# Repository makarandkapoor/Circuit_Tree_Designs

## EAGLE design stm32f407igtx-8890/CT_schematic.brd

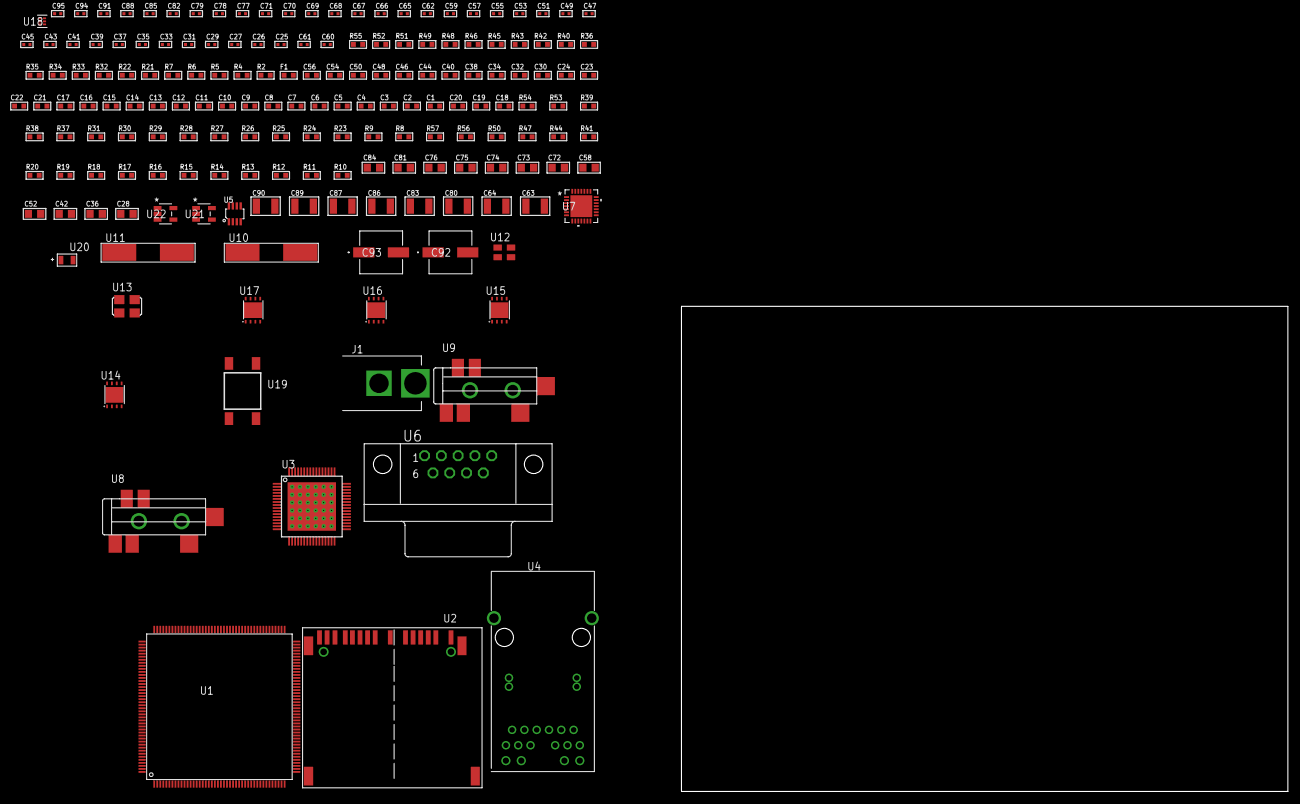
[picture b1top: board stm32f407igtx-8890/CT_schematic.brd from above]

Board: 2 copper layers, 100.0 x 80.0 mm, 174 parts (0 on the bottom side), 99 nets, no tracks yet.

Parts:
C1, C24, C30, C32, C34, C38, C40, C44, C46, C48, C50, C54, C56: 1e-06; C0603
C2, C3, C4, C5, C6, C7, C8, C9, C10, C11, C12, C13, C14, C15, C16, C17, C21, C22: 1e-07; C0603
C18: 4.7e-06; C0603
C19, C20: 2.2e-06; C0603
C23: 1e-08; C0603
C25, C26: 1e-11; C0402
C27, C29, C31, C33, C35, C39, C41, C45, C47, C49, C51, C55, C57, C62, C67, C68, C69, C70, C71, C91: 1e-07; C0402
C28, C36, C42, C52, C58, C72, C73, C74, C75, C76, C81, C84: 1e-05; C0805
C37, C43, C53, C59, C77, C78, C79, C82, C85, C88, C94, C95: 1e-08; C0402
C60, C61: 2.7e-11; C0402
C63, C64: 2.2e-05; C1210
C65, C66: 1e-09; C0402
C80, C83, C86, C87, C89, C90: 1e-05; C1210
C92, C93: 0.0001; EXV-9H
F1: 240.0; L0603
J1: PJ-037B; PJ-037B_PACKAGE
R2, R43, R46, R49, R52: 1000.0; R0603
R4, R5: 4700.0; R0603
R6, R7: 2200.0; R0603
R8, R9, R23, R25, R26, R27, R28, R29, R30, R31, R53, R54: 10000.0; R0603
R10, R11, R12, R13, R14, R15, R16, R17, R18, R19, R20, R41, R44, R47, R50: 100000.0; R0603
R21, R22: 200.0; R0603
R24: 11000.0; R0603
R32, R34: 5760.0; R0603
R33, R35: 2490.0; R0603
R36: 120.0; R0603
R37, R38, R39: 47000.0; R0603
R40: 680.0; R0603
R42: 100.0; R0603
R45: 806.0; R0603
R48: 1500.0; R0603
R51: 2231.0; R0603
R55: 9100.0; R0603
R56: 680000.0; R0603
R57: 120000.0; R0603
U1: STM32F407IGT6; LQFP176
U2: 10100565
U3: DP83867IRPAPT; HTQFP-64-EXP
U4: 7499511611A
U5: MAX3051EKA+T; SOT-23-8
U6: 182-009-113R531; 182-009-MALE
U7: WM8731CLSEFL; QFN-28
U8, U9: SJ-43515TS-SMT-TR
U10, U11: ABLS-25.000MHZ-B2F-T
U12: ASEK-32.768KHz-ECST; ASEK
U13: ASFL1-12.288MHZ-EC-T; ASFL1
U14, U15, U16, U17: LP3878SDX-ADJ/NOPB; WSON-8
U18: TPS3895ADRYR; SON-6
U19: 4-1437565-2; SW_4-1437565-2
U20: Q65110A2395; LGM67K-G1J2-24-Z
U21, U22: nc7sz125m5x; NC7SZ125M5X

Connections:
CLK_CRYSTAL_U1_29: C25.1, U1.29, U10.1
CLK_CRYSTAL_U1_30: C26.1, U1.30, U10.2
CLK_CRYSTAL_U3_18: C60.1, U3.18, U11.2
CLK_CRYSTAL_U3_19: C61.1, U3.19, U11.1
CLK_U1_9: U1.9, U12.3
CLK_U7_1: U7.1, U13.3
GND: C1.2, C2.2, C3.2, C4.2, C5.2, C6.2, C7.2, C8.2, C9.2, C10.2, C11.2, C12.2, C13.2, C14.2, C15.2, C16.2, C17.2, C18.2, C19.2, C20.2, C21.2, C22.2, C23.2, C24.2, C25.2, C26.2, C27.2, C28.2, C29.2, C30.2, C31.2, C32.2, C33.2, C34.2, C35.2, C36.2, C37.2, C38.2, C39.2, C40.2, C41.2, C42.2, C43.2, C44.2, C45.2, C46.2, C47.2, C48.2, C49.2, C50.2, C51.2, C52.2, C53.2, C54.2, C55.2, C56.2, C57.2, C58.2, C59.2, C60.2, C61.2, C62.2, C66.2, C67.2, C68.2, C69.2, C70.2, C71.2, C72.2, C73.2, C74.2, C75.2, C76.2, C77.2, C78.2, C79.2, C80.2, C81.2, C82.2, C83.2, C84.2, C85.2, C86.2, C87.2, C88.2, C89.2, C90.2, C91.2, C92.2, C93.2, C94.2, C95.2, J1.2, R2.2, R8.2, R24.2, R25.2, R26.2, R27.2, R28.2, R29.2, R30.2, R31.2, R33.2, R35.2, R37.2, R38.2, R39.2, R43.2, R46.2, R49.2, R52.2, R55.2, R57.2, U1.14, U1.22, U1.37, U1.48, U1.61, U1.71, U1.90, U1.102, U1.113, U1.126, U1.135, U1.148, U1.158, U2.6, U2.10, U2.12, U2.16, U2.17, U2.20, U2.21, U3.EXP, U4.17, U4.20, U4.Z1, U4.Z2, U5.2, U5.8, U6.5, U7.4, U7.15, U7.19, U7.25, U7.26, U7.29, U8.1, U9.1, U12.2, U13.2, U14.3, U14.PAD, U15.3, U15.PAD, U16.3, U16.PAD, U17.3, U17.PAD, U18.2, U20.C, U21.1, U21.3, U22.1, U22.3
NET_U1_31: R5.1, U1.31, U22.4
NET_U1_33: R6.1, U1.33, U3.20
NET_U1_39: C21.1, C22.1, C23.1, C24.1, F1.1, U1.38, U1.39
NET_U1_42: R7.1, U1.42, U3.21
NET_U1_81: C19.1, U1.81
NET_U1_125: C20.1, U1.125
NET_U1_166: R8.1, U1.166
NET_U1_171: R9.1, U1.171
NET_U1_176: U19.3, U19.4
NET_U2_1: R12.1, U2.1
NET_U2_2: R11.1, U2.2
NET_U2_18: U2.18, U2.19
NET_U3_15: R24.1, U3.15
NET_U3_24: R30.1, U3.24
NET_U3_25: R31.1, U3.25
NET_U3_31: R26.1, U3.31
NET_U3_32: R27.1, U3.32
NET_U3_33: R28.1, U3.33
NET_U3_34: R29.1, U3.34
NET_U3_40: R25.1, U3.40
NET_U3_48: R34.1, R35.1, U3.48
NET_U3_59: R4.1, U3.59, U21.4
NET_U3_60: R23.1, U3.60
NET_U4_2: U3.11, U4.2
NET_U4_3: U3.10, U4.3
NET_U4_4: U3.5, U4.4
NET_U4_5: U3.6, U4.5
NET_U4_6: C29.1, U4.1, U4.6, U4.7, U4.12
NET_U4_8: U3.13, U4.8
NET_U4_9: U3.14, U4.9
NET_U4_10: U3.3, U4.10
NET_U4_11: U3.2, U4.11
NET_U4_18: R21.1, U4.18
NET_U4_19: R22.1, U4.19
NET_U5_6: R36.2, U5.6
NET_U6_2: R36.2, U5.6, U6.2
NET_U6_3: R36.1, U5.7, U6.3
NET_U7_20: C71.1, C76.1, U7.20
NET_U8_2: C64.1, R38.1, U8.2
NET_U8_5: C63.1, R37.1, U8.5
NET_U9_5: C65.1, C66.1, R39.1, R40.1, U9.5
NET_U14_1: C79.1, U14.1
NET_U14_6: R42.2, R43.1, U14.6
NET_U14_8: R41.1, U14.8
NET_U15_1: C82.1, U15.1
NET_U15_6: R45.2, R46.1, U15.6
NET_U15_8: R44.1, U15.8
NET_U16_1: C85.1, U16.1
NET_U16_6: R48.2, R49.1, U16.6
NET_U16_8: R47.1, U16.8
NET_U17_1: C88.1, U17.1
NET_U17_6: R51.2, R52.1, U17.6
NET_U17_8: R50.1, U17.8
NET_U18_1: R54.1, R55.1, U18.1
NET_U18_3: R56.2, R57.1, U18.3
NET_U18_4: R53.1, U18.4, U21.2, U22.2
NET_U19_1: R2.1, U19.1, U19.2
PROC_CAN1_RX: U1.11, U5.4
PROC_CAN1_TX: U1.123, U5.1
PROC_ETH_COL: U1.44, U3.55
PROC_ETH_CRS: U1.40, U3.56
PROC_ETH_RXD0: R32.1, R33.1, U1.54, U3.44
PROC_ETH_RXD1: U1.55, U3.45
PROC_ETH_RXD2: U1.56, U3.46
PROC_ETH_RXD3: U1.57, U3.47
PROC_ETH_RX_CLK: U1.41, U3.43
PROC_ETH_RX_DV: U1.53, U3.53
PROC_ETH_RX_ER: U1.12, U3.54
PROC_ETH_TXD0: U1.92, U3.38
PROC_ETH_TXD1: U1.93, U3.37
PROC_ETH_TXD2: U1.34, U3.36
PROC_ETH_TXD3: U1.1, U3.35
PROC_ETH_TX_CLK: U1.35, U3.30
PROC_ETH_TX_EN: U1.80, U3.52
PROC_I2S2_CK: U1.79, U7.7
PROC_I2S2_EXT_SD: U1.94, U7.10
PROC_I2S2_SD: U1.95, U7.8
PROC_I2S2_WS: U1.131, U7.9, U7.11
PROC_SDIO_CK: R10.1, U1.141, U2.8
PROC_SDIO_D0: R13.1, U1.117, U2.4
PROC_SDIO_D1: R14.1, U1.118, U2.3
PROC_SDIO_D2: R15.1, U1.139, U2.15
PROC_SDIO_D3: R16.1, U1.140, U2.14
PROC_SDIO_D4: R17.1, U1.167, U2.13
PROC_SDIO_D5: R18.1, U1.168, U2.11
PROC_SDIO_D6: R19.1, U1.115, U2.7
PROC_SDIO_D7: R20.1, U1.116, U2.5
VCC_S1_12V3: C80.1, C83.1, C86.1, C89.1, C92.1, C93.1, J1.1, R41.2, R44.2, R47.2, R50.2, U14.4, U15.4, U16.4, U17.4
VCC_TIER1_1V1: C44.1, C45.1, C46.1, C47.1, C48.1, C49.1, C50.1, C51.1, C52.1, C53.1, C81.1, R42.1, U3.8, U3.29, U3.42, U3.58, U14.5
VCC_TIER1_1V8: C27.1, C28.1, C54.1, C55.1, C56.1, C57.1, C58.1, C59.1, C67.1, C69.1, C70.1, C72.1, C74.1, C75.1, C84.1, C94.1, C95.1, R10.2, R11.2, R12.2, R13.2, R14.2, R15.2, R16.2, R17.2, R18.2, R19.2, R20.2, R45.1, U2.9, U3.17, U3.64, U7.5, U7.12, U7.18, U15.5, U21.5, U22.5
VCC_TIER1_2V5: C38.1, C39.1, C40.1, C41.1, C42.1, C43.1, C87.1, R48.1, U3.4, U3.12, U16.5
VCC_TIER1_3V3: C1.1, C2.1, C3.1, C4.1, C5.1, C6.1, C7.1, C8.1, C9.1, C10.1, C11.1, C12.1, C13.1, C14.1, C15.1, C16.1, C17.1, C18.1, C30.1, C31.1, C32.1, C33.1, C34.1, C35.1, C36.1, C37.1, C62.1, C68.1, C73.1, C77.1, C78.1, C90.1, C91.1, F1.2, R4.2, R5.2, R6.2, R7.2, R9.2, R23.2, R32.2, R34.2, R51.1, R53.2, R54.2, R56.1, U1.6, U1.15, U1.23, U1.36, U1.49, U1.62, U1.72, U1.82, U1.91, U1.103, U1.114, U1.127, U1.136, U1.149, U1.159, U1.172, U3.23, U3.41, U3.57, U5.3, U7.3, U12.4, U13.4, U17.5, U18.6

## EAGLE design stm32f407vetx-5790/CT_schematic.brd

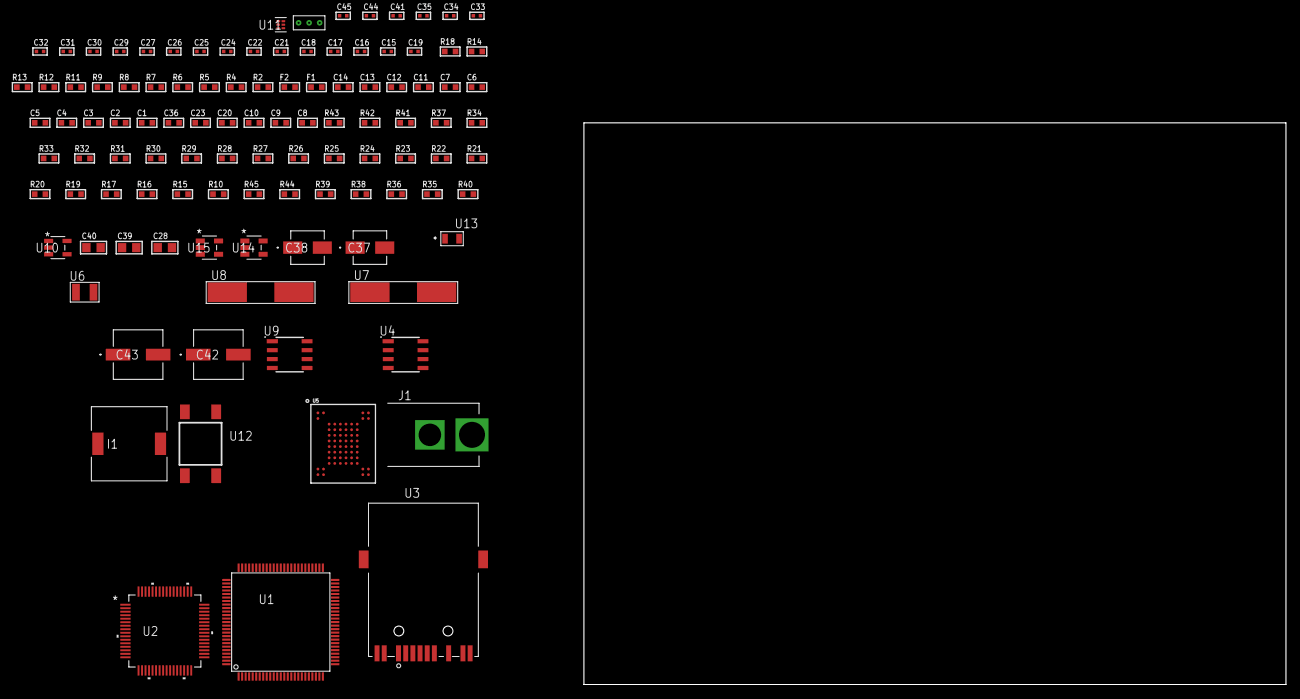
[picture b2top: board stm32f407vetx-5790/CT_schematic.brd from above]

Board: 2 copper layers, 100.0 x 80.0 mm, 108 parts (0 on the bottom side), 72 nets, no tracks yet.

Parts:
C1, C14: 1e-06; C0603
C2, C3, C4, C5, C6, C7, C11, C12: 1e-07; C0603
C8: 4.7e-06; C0603
C9, C10, C20, C23, C36: 2.2e-06; C0603
C13: 1e-08; C0603
C15, C16, C17, C18: 1e-11; C0402
C19: 1.8e-08; C0402
C21, C24, C26, C27, C29, C30, C32, C33, C34, C35, C41: 1e-07; C0402
C22, C25, C31, C44, C45: 1e-08; C0402
C28, C39, C40: 1e-05; C0805
C37: 1e-06; EXV-9B
C38: 2.2e-06; EXV-9B
C42, C43: 0.0001; EXV-9H
F1: 240.0; L0603
F2: 510.0; L0603
I1: 5.2e-06; DR1040
J1: PJ-037B; PJ-037B_PACKAGE
R2: 1000.0; R0603
R4, R5: 4700.0; R0603
R6, R7, R8, R9: 2200.0; R0603
R10, R15, R16, R17, R19, R20, R21, R22, R23, R24, R25, R26, R27, R28, R29, R30, R31, R32, R33, R34, R41, R42: 10000.0; R0603
R11, R12: 0.1; R0603
R13, R14: 200.0; R0603
R18: 1270.0; R0603
R35, R36, R38: 100000.0; R0603
R37: 47000.0; R0603
R39: 220000.0; R0603
R40: 1000000.0; R0603
R43: 82000.0; R0603
R44: 300000.0; R0603
R45: 120000.0; R0603
U1: STM32F407VET6; LQFP100
U2: BCM5221KPT; TQFP64_10X10MC
U3: 7498011122R
U4: AT24C02D-SSHM-T; AT24C02D
U5: mt29f4g08abbdah4; VFBGA-63
U6: ABS07-32.768KHZ-7-T
U7, U8: ABLS-25.000MHZ-B2F-T
U9: LP2954AIMX/NOPB; LP2954
U10: ltc3406es5; TSOT-23-5
U11: TPS3895ADRYR; SON-6
U12: 4-1437565-2; SW_4-1437565-2
U13: Q65110A2395; LGM67K-G1J2-24-Z
U14, U15: nc7sz125m5x; NC7SZ125M5X
U16: Dummy; DUMMY_PACKAGE_218

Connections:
CLK_CRYSTAL_U1_8: C15.1, U1.8, U6.1
CLK_CRYSTAL_U1_9: C16.1, U1.9, U6.2
CLK_CRYSTAL_U1_12: C17.1, U1.12, U7.1
CLK_CRYSTAL_U1_13: C18.1, U1.13, U7.2
CLK_CRYSTAL_U2_5: U2.5, U8.2
CLK_CRYSTAL_U2_6: U2.6, U8.1
GND: C1.2, C2.2, C3.2, C4.2, C5.2, C6.2, C7.2, C8.2, C9.2, C10.2, C11.2, C12.2, C13.2, C14.2, C15.2, C16.2, C17.2, C18.2, C19.2, C20.2, C21.2, C22.2, C23.2, C24.2, C25.2, C26.2, C27.2, C28.2, C29.2, C30.2, C31.2, C32.2, C33.2, C34.2, C35.2, C36.2, C37.2, C38.2, C39.2, C40.1, C40.2, C41.2, C42.2, C43.2, C44.2, C45.2, J1.2, R2.2, R10.2, R11.2, R12.2, R15.2, R17.2, R18.2, R21.2, R22.2, R23.2, R24.2, R26.2, R28.2, R29.2, R38.2, R39.2, R43.2, R45.2, U1.10, U1.20, U1.27, U1.74, U1.99, U2.7, U2.24, U2.29, U2.32, U2.40, U2.45, U2.54, U2.63, U3.10, U3.12, U4.4, U5.C5, U5.F7, U5.K3, U5.K8, U9.4, U10.2, U11.2, U13.C, U14.1, U14.3, U15.1, U15.3, U16.1
NET_U1_14: R5.1, U1.14, U15.4
NET_U1_22: C11.1, C12.1, C13.1, C14.1, F1.1, U1.21, U1.22
NET_U1_49: C9.1, U1.49
NET_U1_73: C10.1, U1.73
NET_U1_92: R6.1, U1.92, U4.6
NET_U1_93: R7.1, U1.93, U4.5
NET_U1_94: R10.1, U1.94
NET_U1_98: U12.3, U12.4
NET_U2_2: C23.1, C24.1, C25.1, U2.2, U2.55
NET_U2_9: R4.1, U2.9, U14.4
NET_U2_10: R19.1, U2.10
NET_U2_11: R20.1, U2.11
NET_U2_12: R21.1, U2.12
NET_U2_13: R22.1, U2.13
NET_U2_14: R23.1, U2.14
NET_U2_16: R17.1, U2.16
NET_U2_18: R25.1, U2.18
NET_U2_23: R18.1, U2.23
NET_U2_27: C20.1, C21.1, C22.1, U2.22, U2.27, U2.28
NET_U2_37: R24.1, U2.37
NET_U2_38: R15.1, U2.38
NET_U2_39: R16.1, U2.39
NET_U3_1: U2.31, U3.1
NET_U3_2: F2.2, U3.2
NET_U3_3: U2.30, U3.3
NET_U3_4: U2.26, U3.4
NET_U3_5: C19.1, F2.1, U3.2, U3.5
NET_U3_6: U2.25, U3.6
NET_U3_8: R12.1, U3.8
NET_U3_9: R13.1, U3.9
NET_U3_11: R14.1, U3.11
NET_U3_12: R13.2, U3.12
NET_U3_13: R11.1, U3.13, U3.14
NET_U4_1: R27.1, U4.1
NET_U4_2: R28.1, U4.2
NET_U4_3: R29.1, U4.3
NET_U4_7: R26.1, U4.7
NET_U5_C3: R34.1, U5.C3
NET_U9_3: R36.1, U9.3
NET_U9_5: R35.1, U9.5
NET_U9_7: R37.2, R38.1, U9.7
NET_U10_3: I1.1, U10.3
NET_U10_5: R39.1, R40.1, U10.5
NET_U10_ATNET_3: I1.2, R40.2
NET_U11_1: R42.1, R43.1, U11.1
NET_U11_3: R44.2, R45.1, U11.3
NET_U11_4: R41.1, U11.4, U14.2, U15.2
NET_U12_1: R2.1, U12.1, U12.2
PROC_FSMC_D0: U1.61, U5.H4
PROC_FSMC_D1: U1.62, U5.J4
PROC_FSMC_D2: U1.81, U5.K4
PROC_FSMC_D3: U1.82, U5.K5
PROC_FSMC_D4: U1.38, U5.K6
PROC_FSMC_D5: U1.39, U5.J7
PROC_FSMC_D6: U1.40, U5.K7
PROC_FSMC_D7: U1.41, U5.J8
PROC_FSMC_NCE2: R31.1, U1.88, U5.C6
PROC_FSMC_NOE: R33.1, U1.85, U5.D4
PROC_FSMC_NWAIT: R30.1, U1.87, U5.C8
PROC_FSMC_NWE: R32.1, U1.86, U5.C7
PROC_TIM1_CH2: U1.42, U16.2
PROC_TIM1_CH4: U1.45, U16.3
VCC_S1_5V2: C37.1, C39.1, C42.1, C43.1, J1.1, R36.2, U9.8, U10.4
VCC_TIER1_1V8: C1.1, C2.1, C3.1, C4.1, C5.1, C6.1, C7.1, C8.1, C31.1, C32.1, C33.1, C34.1, C35.1, C36.1, C38.1, C41.1, C44.1, C45.1, F1.2, R5.2, R6.2, R7.2, R8.2, R9.2, R27.2, R30.2, R31.2, R32.2, R33.2, R34.2, R35.2, R37.1, R41.2, R42.2, R44.1, U1.6, U1.11, U1.19, U1.28, U1.50, U1.75, U1.100, U4.8, U5.D3, U5.G4, U5.H8, U5.J6, U9.1, U11.6, U14.5, U15.5
VCC_TIER1_3V3: C26.1, C27.1, C28.1, C29.1, C30.1, C40.2, I1.2, R4.2, R16.2, R19.2, R20.2, R25.2, R40.2, U2.1, U2.3, U2.46

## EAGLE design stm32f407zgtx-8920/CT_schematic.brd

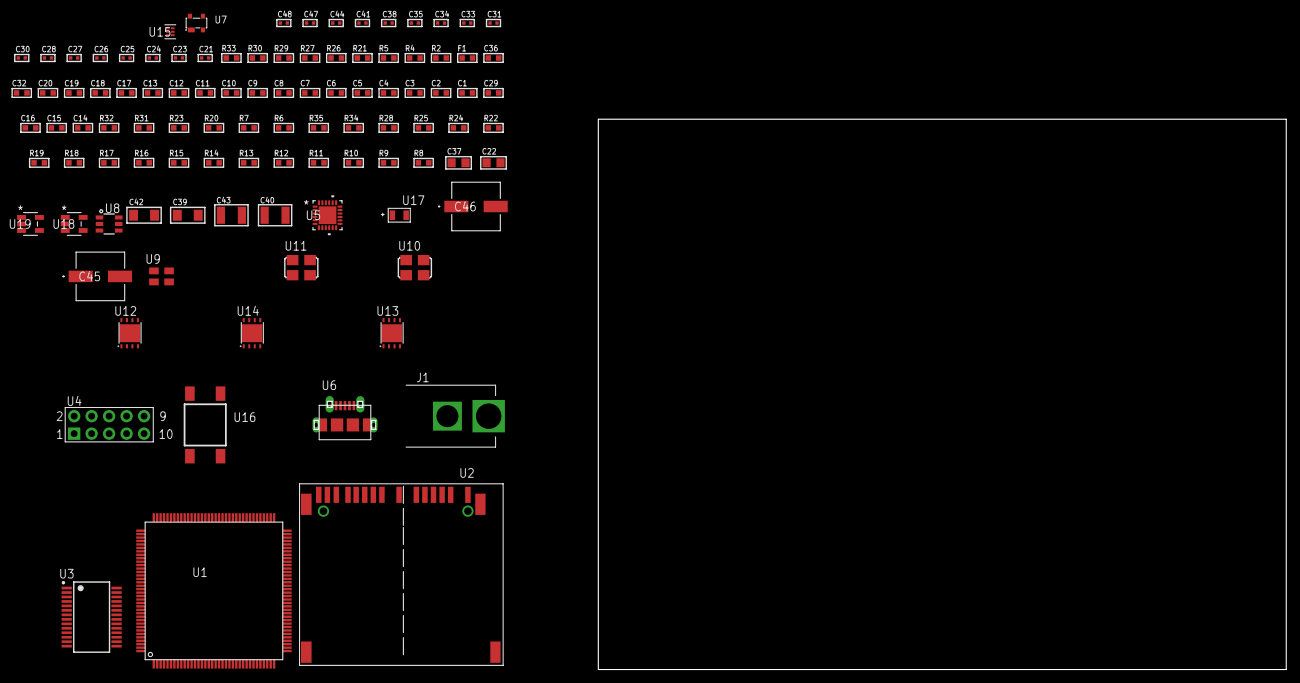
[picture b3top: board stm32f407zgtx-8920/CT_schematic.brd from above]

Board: 2 copper layers, 102 parts (0 on the bottom side), 73 nets, no tracks yet.

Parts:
C1, C20, C32, C36: 1e-06; C0603
C2, C3, C4, C5, C6, C7, C8, C9, C10, C11, C12, C13, C17, C18: 1e-07; C0603
C14: 4.7e-06; C0603
C15, C16, C29: 2.2e-06; C0603
C19: 1e-08; C0603
C21, C23, C24, C25, C26, C27, C44: 1e-07; C0402
C22, C37: 1e-05; C0805
C28, C30, C31, C33, C34, C35, C38, C41, C47, C48: 1e-08; C0402
C39, C42: 1e-05; C1206
C40, C43: 1e-05; C1210
C45, C46: 0.0001; EXV-9H
F1: 240.0; L0603
J1: PJ-037B; PJ-037B_PACKAGE
R2, R27, R30: 1000.0; R0603
R4, R5: 4700.0; R0603
R6, R7, R31, R32: 10000.0; R0603
R8, R9, R10, R11, R12, R13, R14, R15, R16, R17, R18, R19, R22, R24, R25, R28: 100000.0; R0603
R20: 47000.0; R0603
R21: 8060.0; R0603
R23: 36000.0; R0603
R26: 2231.0; R0603
R29: 3900.0; R0603
R33: 9100.0; R0603
R34: 680000.0; R0603
R35: 120000.0; R0603
U1: STM32F407ZGT6; LQFP144
U2: 10100565
U3: ST3241EBPR; SSOP-28
U4: HTSS-105-01-G-D
U5: USB3317C-CP-TR; QFN-24
U6: 47590-0001; MICRO_USB_AB
U7: prtr5v0u2ax; SOT143B
U8: MAX4995AAUT+T; SOT-23-6
U9: ASEK-32.768KHz-ECST; ASEK
U10: ASFL1-25MHZ-NCS; ASFL1
U11: ASFL1-26MHZ-NCS; ASFL1
U12: LP2951ACSDX/NOPB; WSON-8
U13, U14: LP3878SDX-ADJ/NOPB; WSON-8
U15: TPS3895ADRYR; SON-6
U16: 4-1437565-2; SW_4-1437565-2
U17: Q65110A2395; LGM67K-G1J2-24-Z
U18, U19: nc7sz125m5x; NC7SZ125M5X

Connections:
CLK_U1_8: U1.8, U9.3
CLK_U1_23: U1.23, U10.3
CLK_U5_23: U5.23, U11.3
GND: C1.2, C2.2, C3.2, C4.2, C5.2, C6.2, C7.2, C8.2, C9.2, C10.2, C11.2, C12.2, C13.2, C14.2, C15.2, C16.2, C17.2, C18.2, C19.2, C20.2, C21.2, C22.2, C23.2, C26.2, C27.2, C28.2, C29.2, C30.2, C31.2, C32.2, C33.2, C34.2, C35.2, C36.2, C37.2, C38.2, C39.2, C40.2, C41.2, C42.2, C43.2, C44.2, C45.2, C46.2, C47.2, C48.2, J1.2, R2.2, R7.2, R20.2, R21.2, R24.2, R27.2, R30.2, R33.2, R35.2, U1.16, U1.31, U1.38, U1.51, U1.61, U1.83, U1.94, U1.107, U1.120, U1.130, U2.6, U2.10, U2.12, U2.16, U2.17, U2.20, U2.21, U3.23, U3.25, U4.9, U5.25, U6.5, U6.6, U6.7, U6.8, U6.9, U7.1, U8.2, U9.2, U10.2, U11.2, U12.3, U12.4, U12.PAD, U13.3, U13.PAD, U14.3, U14.PAD, U15.2, U17.C, U18.1, U18.3, U19.1, U19.3
NET_U1_25: R4.1, U1.25, U18.4
NET_U1_33: C17.1, C18.1, C19.1, C20.1, F1.1, U1.32, U1.33
NET_U1_71: C15.1, U1.71
NET_U1_106: C16.1, U1.106
NET_U1_138: R7.1, U1.138
NET_U1_142: U16.3, U16.4
NET_U1_143: R6.1, U1.143
NET_U2_1: R10.1, U2.1
NET_U2_2: R9.1, U2.2
NET_U2_18: U2.18, U2.19
NET_U3_1: C25.1, U3.1
NET_U3_2: C25.2, U3.2
NET_U3_3: C27.1, U3.3
NET_U3_22: R19.1, U3.22
NET_U3_24: C24.2, U3.24
NET_U3_27: C26.1, U3.27
NET_U3_28: C24.1, U3.28
NET_U4_3: U3.4, U4.3
NET_U4_4: U3.5, U4.4
NET_U4_5: U3.9, U4.5
NET_U4_6: U3.10, U4.6
NET_U5_4: C29.1, U5.4
NET_U5_22: R5.1, U5.22, U19.4
NET_U5_24: R21.1, U5.24
NET_U6_1: C32.1, U5.2, U6.1, U7.4, U8.1
NET_U6_2: U5.5, U6.2, U7.3
NET_U6_3: U5.6, U6.3, U7.2
NET_U6_4: U5.1, U6.4
NET_U8_3: R20.1, U8.3
NET_U8_4: U5.7, U8.4
NET_U12_5: R22.1, U12.5
NET_U12_7: R23.2, R24.1, U12.7
NET_U13_1: C38.1, U13.1
NET_U13_6: R26.2, R27.1, U13.6
NET_U13_8: R25.1, U13.8
NET_U14_1: C41.1, U14.1
NET_U14_6: R29.2, R30.1, U14.6
NET_U14_8: R28.1, U14.8
NET_U15_1: R32.1, R33.1, U15.1
NET_U15_3: R34.2, R35.1, U15.3
NET_U15_4: R31.1, U15.4, U18.2, U19.2
NET_U16_1: R2.1, U16.1, U16.2
PROC_SDIO_CK: R8.1, U1.113, U2.8
PROC_SDIO_D0: R11.1, U1.98, U2.4
PROC_SDIO_D1: R12.1, U1.99, U2.3
PROC_SDIO_D2: R13.1, U1.111, U2.15
PROC_SDIO_D3: R14.1, U1.112, U2.14
PROC_SDIO_D4: R15.1, U1.139, U2.13
PROC_SDIO_D5: R16.1, U1.140, U2.11
PROC_SDIO_D6: R17.1, U1.96, U2.7
PROC_SDIO_D7: R18.1, U1.97, U2.5
PROC_UART4_RX: U1.35, U3.19
PROC_UART4_TX: U1.34, U3.14
PROC_USB_OTG_HS_ULPI_CK: U1.41, U5.12
PROC_USB_OTG_HS_ULPI_D0: U1.37, U5.16
PROC_USB_OTG_HS_ULPI_D1: U1.46, U5.15
PROC_USB_OTG_HS_ULPI_D2: U1.47, U5.14
PROC_USB_OTG_HS_ULPI_D3: U1.69, U5.13
PROC_USB_OTG_HS_ULPI_D4: U1.70, U5.11
PROC_USB_OTG_HS_ULPI_D5: U1.73, U5.10
PROC_USB_OTG_HS_ULPI_D6: U1.74, U5.9
PROC_USB_OTG_HS_ULPI_D7: U1.135, U5.8
PROC_USB_OTG_HS_ULPI_DIR: U1.28, U5.19
PROC_USB_OTG_HS_ULPI_NXT: U1.29, U5.18
PROC_USB_OTG_HS_ULPI_STP: U1.26, U5.20
VCC_S1_10V2: C36.1, C39.1, C42.1, C45.1, C46.1, J1.1, R25.2, R28.2, U12.8, U13.4, U14.4
VCC_TIER1_1V8: C21.1, C22.1, C31.1, C37.1, C47.1, C48.1, R8.2, R9.2, R10.2, R11.2, R12.2, R13.2, R14.2, R15.2, R16.2, R17.2, R18.2, R22.2, R23.1, U2.9, U5.21, U12.1, U18.5, U19.5
VCC_TIER1_3V3: C1.1, C2.1, C3.1, C4.1, C5.1, C6.1, C7.1, C8.1, C9.1, C10.1, C11.1, C12.1, C13.1, C14.1, C23.1, C28.1, C30.1, C33.1, C34.1, C35.1, C40.1, C44.1, F1.2, R4.2, R5.2, R6.2, R19.2, R26.1, R31.2, R32.2, R34.1, U1.6, U1.17, U1.30, U1.39, U1.52, U1.62, U1.72, U1.84, U1.95, U1.108, U1.121, U1.131, U1.144, U3.26, U5.3, U5.17, U9.4, U10.4, U11.4, U13.5, U15.6
VCC_TIER1_5V0: C43.1, R29.1, U8.5, U14.5

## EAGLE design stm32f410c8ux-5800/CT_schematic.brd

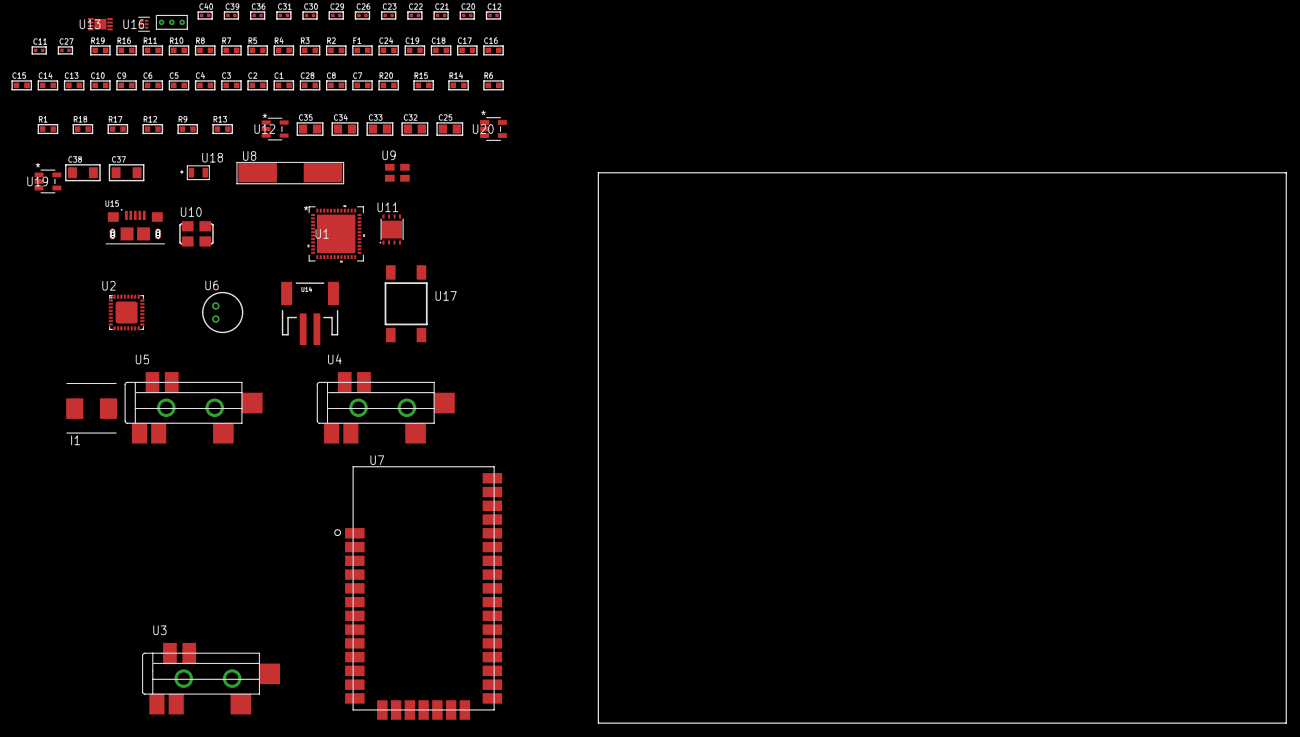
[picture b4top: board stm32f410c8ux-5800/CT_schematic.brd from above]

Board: 2 copper layers, 83 parts (0 on the bottom side), 50 nets, no tracks yet.

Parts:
C1, C10, C13, C14, C15, C16, C17, C18, C19, C24: 1e-06; C0603
C2, C3, C4, C5, C6: 1e-07; C0603
C7: 4.7e-06; C0603
C8: 2.2e-06; C0603
C9: 1e-08; C0603
C11, C12: 1e-11; C0402
C20, C21, C22, C23, C26, C36: 1e-07; C0402
C25, C32, C33, C34, C35: 1e-05; C0805
C27: 4.7e-11; C0402
C28: 8.2e-12; C0603
C29, C30, C31, C39, C40: 1e-08; C0402
C37, C38: 1e-05; C1206
F1: 240.0; L0603
I1: 2e-06; WE-HCI_7030/7040/7050
R1, R6, R14, R15, R20: 10000.0; R0603
R2, R11: 1000.0; R0603
R3: 1600.5; R0603
R4, R5: 4700.0; R0603
R7, R8: 1270.0; R0603
R9: 100000.0; R0603
R10: 200.0; R0603
R12: 220000.0; R0603
R13: 1000000.0; R0603
R16: 9100.0; R0603
R17: 680000.0; R0603
R18: 120000.0; R0603
R19: 2000.0; R0603
U1: STM32F410C8U6; UFQFPN48
U2: SGTL5000XNAA3; QFN-32
U3, U4, U5: SJ-43515TS-SMT-TR
U6: WM-64PCT; WM-64PC
U7: XB24CZ7UIS-004
U8: ABLS-25.000MHZ-B2F-T
U9: ASEK-32.768KHz-ECST; ASEK
U10: ASFL-24.57MHZ-NCS; ASFL1
U11: LP3878SDX-ADJ/NOPB; WSON-8
U12: ltc3406es5; TSOT-23-5
U13: MCP73831T-2ACI/MC; DFN8_2X3MC
U14: S2B-PH-SM4-TB(LF)(SN); JST-2-SMD
U15: 10118193-0001LF; FCI_10118193-0001LF
U16: TPS3895ADRYR; SON-6
U17: 4-1437565-2; SW_4-1437565-2
U18: Q65110A2395; LGM67K-G1J2-24-Z
U19, U20: nc7sz125m5x; NC7SZ125M5X
U21: Dummy; DUMMY_PACKAGE_166

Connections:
CLK_CRYSTAL_U1_5: C11.1, U1.5, U8.1
CLK_CRYSTAL_U1_6: C12.1, U1.6, U8.2
CLK_U1_3: U1.3, U9.3
CLK_U2_21: U2.21, U10.3
GND: C1.2, C2.2, C3.2, C4.2, C5.2, C6.2, C7.2, C8.2, C9.2, C10.2, C11.2, C12.2, C20.2, C21.2, C22.2, C23.2, C24.2, C25.2, C26.2, C27.2, C28.2, C29.2, C30.2, C31.2, C32.2, C33.2, C34.2, C35.1, C35.2, C36.2, C37.2, C38.2, C39.2, C40.2, R2.2, R6.2, R8.2, R11.2, R12.2, R16.2, R18.2, R19.2, U1.8, U1.23, U1.35, U1.47, U1.49, U2.1, U2.3, U2.7, U2.EXP, U4.1, U5.1, U6.2, U7.1, U7.11, U7.13, U7.22, U7.35, U9.2, U10.2, U11.3, U11.PAD, U12.2, U13.6, U13.9, U14.2, U15.5, U15.6, U15.7, U15.8, U15.9, U16.2, U18.C, U19.1, U19.3, U20.1, U20.3, U21.1
INPUT_USBPOWER_5V: C37.1, R20.2, U13.1, U13.2, U15.1
NET_U1_7: R5.1, U1.7, U20.4
NET_U1_9: C3.1, C9.1, C10.1, F1.1, U1.9
NET_U1_22: C8.1, U1.22
NET_U1_44: R6.1, U1.44
NET_U1_45: R3.1, U1.45, U18.A
NET_U1_46: R1.1, U1.46, U17.3, U17.4
NET_U2_10: C23.1, U2.10
NET_U2_29: R7.1, U2.29
NET_U2_31: R8.1, U2.31
NET_U3_1: U2.4, U3.1
NET_U3_2: U2.2, U3.2
NET_U3_5: U2.6, U3.5
NET_U4_2: C14.1, U4.2
NET_U4_5: C13.1, U4.5
NET_U5_2: C16.1, C17.1, U5.2
NET_U5_5: C15.1, U5.5
NET_U5_13: C16.2, C17.2
NET_U6_1: C18.1, C19.1, C24.1, U2.16, U6.1
NET_U6_15: C18.2, C19.2
NET_U7_6: R4.1, U7.6, U19.4
NET_U11_1: C31.1, U11.1
NET_U11_6: R10.2, R11.1, U11.6
NET_U11_8: R9.1, U11.8
NET_U12_3: I1.1, U12.3
NET_U12_5: R12.1, R13.1, U12.5
NET_U12_ATNET_3: I1.2, R13.2
NET_U13_5: R20.1, U13.5
NET_U13_8: R19.1, U13.8
NET_U16_1: R15.1, R16.1, U16.1
NET_U16_3: R17.2, R18.1, U16.3
NET_U16_4: R14.1, U16.4, U19.2, U20.2
NET_U17_1: R2.1, U17.1, U17.2
PROC_ADC1_IN1: U1.11, U21.3
PROC_ADC1_IN2: U1.12, U21.2
PROC_I2S1_CK: U1.15, U2.24
PROC_I2S1_SD: U1.17, U2.26
PROC_I2S1_WS: U1.14, U2.23
PROC_SPI1_MISO: U1.16, U7.17
PROC_SPI1_MOSI: U1.41, U7.16
PROC_SPI1_NSS: U1.38, U7.15
PROC_SPI1_SCK: U1.39, U7.14
VCC_S1_3V7: C32.1, C34.1, C38.1, R9.2, U11.4, U12.4, U13.3, U13.4, U14.1
VCC_TIER1_1V2: C20.1, C33.1, R10.1, U2.30, U11.5
VCC_TIER1_3V3: C1.1, C2.1, C4.1, C5.1, C6.1, C7.1, C21.1, C22.1, C25.1, C26.1, C27.1, C28.1, C29.1, C30.1, C35.2, C36.1, C39.1, C40.1, F1.2, I1.2, R1.2, R3.2, R4.2, R5.2, R7.2, R13.2, R14.2, R15.2, R17.1, U1.1, U1.24, U1.36, U1.48, U2.5, U2.20, U7.2, U7.27, U9.4, U10.4, U16.6, U19.5, U20.5

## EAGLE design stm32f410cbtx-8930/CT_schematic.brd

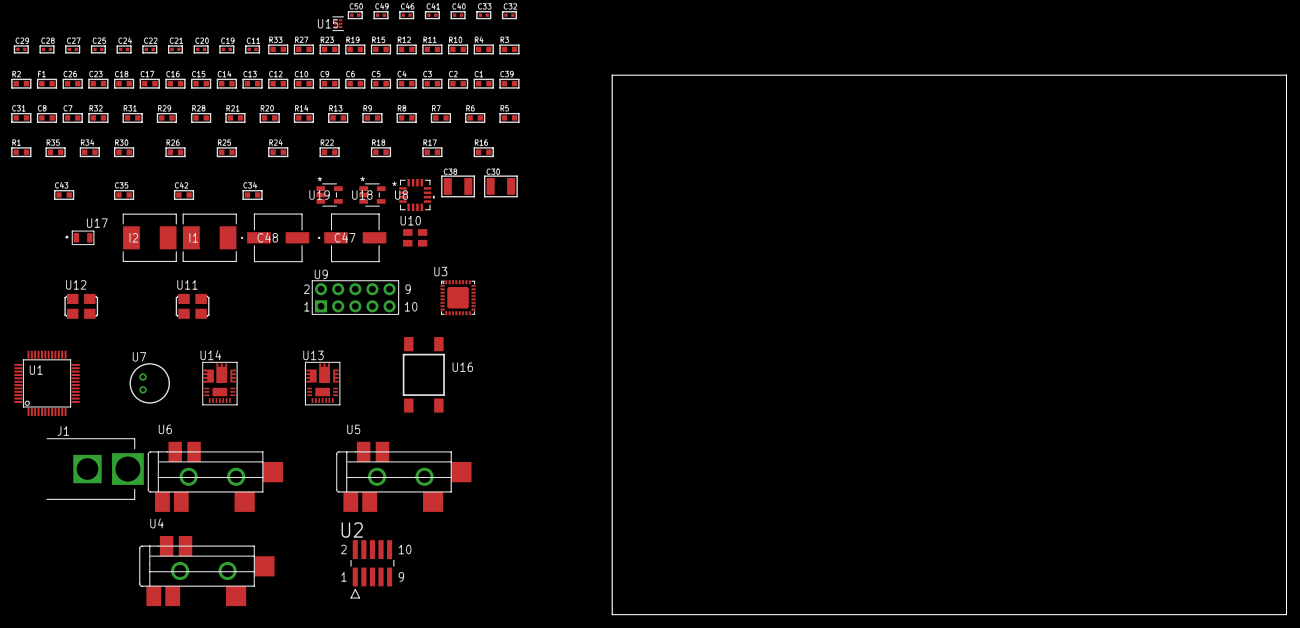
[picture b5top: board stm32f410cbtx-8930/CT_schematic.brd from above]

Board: 2 copper layers, 100.0 x 80.0 mm, 104 parts (0 on the bottom side), 68 nets, no tracks yet.

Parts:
C1, C10, C12, C13, C14, C15, C16, C17, C18, C23, C26: 1e-06; C0603
C2, C3, C4, C5, C6: 1e-07; C0603
C7: 4.7e-06; C0603
C8, C31, C39: 2.2e-06; C0603
C9: 1e-08; C0603
C11, C19, C20, C21, C22, C24, C25, C32, C33, C40, C41, C46: 1e-07; C0402
C27, C28, C29, C49, C50: 1e-08; C0402
C30, C38: 0.0001; C1210
C34, C42: 8.5935703950126e-09; R0603
C35, C43: 2.929626271027e-07; R0603
C47, C48: 0.0001; EXV-9H
F1: 240.0; L0603
I1, I2: 6.8e-07; IND25X25CZ
J1: PJ-037B; PJ-037B_PACKAGE
R1, R5, R6, R7, R8, R9, R13, R14, R31, R32: 10000.0; R0603
R2: 1000.0; R0603
R3: 1600.5; R0603
R4: 4700.0; R0603
R10: 5.0; R0603
R11, R12: 1270.0; R0603
R15, R23: 0.1; R0603
R16, R24: 4030.2416170974; R0603
R17: 2878.7440122125; R0603
R18, R26: 59.319518072289; R0603
R19, R27: 130.0; R0603
R20, R28: 39000.0; R0603
R21, R29: 49900.0; R0603
R22, R30: 5216.2133333333; R0603
R25: 719.68600305311; R0603
R33: 9100.0; R0603
R34: 680000.0; R0603
R35: 120000.0; R0603
U1: STM32F410CBT3; LQFP48
U2: FTSH-105-01-L-DV-K; SAMTEC_FTSH-105-01-L-DV-K
U3: SGTL5000XNAA3; QFN-32
U4, U5, U6: SJ-43515TS-SMT-TR
U7: WM-64PCT; WM-64PC
U8: TSC2046IRGVR; VQFN-16
U9: HTSS-105-01-G-D
U10: ASEK-32.768KHz-ECST; ASEK
U11: ASFL-24.57MHZ-NCS; ASFL1
U12: ASFL1-25MHZ-NCS; ASFL1
U13, U14: IR3899MTR1PBF
U15: TPS3895ADRYR; SON-6
U16: 4-1437565-2; SW_4-1437565-2
U17: Q65110A2395; LGM67K-G1J2-24-Z
U18, U19: nc7sz125m5x; NC7SZ125M5X

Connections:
CLK_U1_3: U1.3, U10.3
CLK_U1_5: U1.5, U12.3
CLK_U3_21: U3.21, U11.3
GND: C1.2, C2.2, C3.2, C4.2, C5.2, C6.2, C7.2, C8.2, C9.2, C10.2, C11.2, C19.2, C20.2, C21.2, C22.2, C23.2, C24.2, C25.2, C26.2, C27.2, C28.2, C29.2, C31.2, C32.2, C33.2, C39.2, C40.2, C41.2, C46.2, C47.2, C48.2, C49.2, C50.2, J1.2, R2.2, R5.2, R10.2, R12.2, R15.1, R15.2, R17.2, R20.2, R22.2, R23.1, R23.2, R25.2, R28.2, R30.2, R33.2, R35.2, U1.8, U1.23, U1.35, U1.46, U2.3, U2.5, U3.1, U3.3, U3.7, U3.EXP, U5.1, U6.1, U7.2, U8.10, U9.9, U10.2, U11.2, U12.2, U13.4, U13.11, U13.17, U14.4, U14.11, U14.17, U15.2, U17.C, U18.2, U18.3, U19.1, U19.3
NET_U1_7: R4.1, U1.7, U19.4
NET_U1_9: C9.1, C10.1, F1.1, U1.9
NET_U1_22: C8.1, U1.22
NET_U1_43: R3.1, U1.43, U17.A
NET_U1_44: R5.1, U1.44
NET_U1_45: R1.1, U1.45, U16.3, U16.4
NET_U1_47: R6.1, U1.47
NET_U2_9: R10.1, U2.9
NET_U3_10: C22.1, U3.10
NET_U3_29: R11.1, U3.29
NET_U3_31: R12.1, U3.31
NET_U4_1: U3.4, U4.1
NET_U4_2: U3.2, U4.2
NET_U4_5: U3.6, U4.5
NET_U5_2: C13.1, U5.2
NET_U5_5: C12.1, U5.5
NET_U6_2: C15.1, C16.1, U6.2
NET_U6_5: C14.1, U6.5
NET_U6_13: C15.2, C16.2
NET_U7_1: C17.1, C18.1, C23.1, U3.16, U7.1
NET_U7_15: C17.2, C18.2
NET_U8_15: R14.1, U8.15
NET_U9_3: U8.7, U9.3
NET_U9_4: U8.9, U9.4
NET_U9_5: U8.6, U9.5
NET_U9_6: U8.8, U9.6
NET_U13_1: C34.1, R16.1, R17.1, R18.1, R19.1, U13.1, U13.8
NET_U13_2: C33.1, U13.2
NET_U13_3: C34.2, C35.1, C35.2, U13.3
NET_U13_5: R20.1, U13.5
NET_U13_10: C31.1, U13.10
NET_U13_12: C30.1, I1.1, U13.12
NET_U13_14: C30.2, U13.14
NET_U13_15: R21.1, R22.1, U13.15
NET_U13_ATNET_3: I1.2, R16.2
NET_U13_ATNET_4: C35.2, R18.2
NET_U14_1: C42.1, R24.1, R25.1, R26.1, R27.1, U14.1, U14.8
NET_U14_2: C41.1, U14.2
NET_U14_3: C42.2, C43.1, C43.2, U14.3
NET_U14_5: R28.1, U14.5
NET_U14_10: C39.1, U14.10
NET_U14_12: C38.1, I2.1, U14.12
NET_U14_14: C38.2, U14.14
NET_U14_15: R29.1, R30.1, U14.15
NET_U14_ATNET_3: I2.2, R24.2
NET_U14_ATNET_4: C43.2, R26.2
NET_U15_1: R32.1, R33.1, U15.1
NET_U15_3: R34.2, R35.1, U15.3
NET_U15_4: R31.1, U15.4, U18.4, U19.2
NET_U16_1: R2.1, U16.1, U16.2
PROC_I2S2_CK: U1.21, U3.24
PROC_I2S2_SD: U1.28, U3.26
PROC_I2S2_WS: U1.25, U3.23
PROC_SPI1_MISO: U1.16, U8.16
PROC_SPI1_MOSI: U1.17, U8.2
PROC_SPI1_NSS: R13.1, U1.14, U8.3
PROC_SPI1_SCK: U1.15, U8.4
PROC_SYS_JTCK_SWCLK: R8.1, U1.37, U2.4
PROC_SYS_JTDO_SWO: U1.39, U2.6
PROC_SYS_JTMS_SWDIO: R9.1, U1.34, U2.2
RST_OUT_U2_JTAG_RST_B: R7.1, U2.10, U18.1
VCC_S1_16V6: C32.1, C40.1, C47.1, C48.1, J1.1, R21.2, R29.2, U13.9, U14.9
VCC_TIER1_1V2: C19.1, I1.2, R16.2, U3.30
VCC_TIER1_3V3: C1.1, C2.1, C3.1, C4.1, C5.1, C6.1, C7.1, C11.1, C20.1, C21.1, C24.1, C25.1, C26.1, C27.1, C28.1, C29.1, C46.1, C49.1, C50.1, F1.2, I2.2, R1.2, R3.2, R4.2, R6.2, R7.2, R8.2, R9.2, R11.2, R13.2, R14.2, R24.2, R31.2, R32.2, R34.1, U1.1, U1.24, U1.36, U1.48, U2.1, U3.5, U3.20, U8.5, U8.14, U10.4, U11.4, U12.4, U15.6, U18.5, U19.5

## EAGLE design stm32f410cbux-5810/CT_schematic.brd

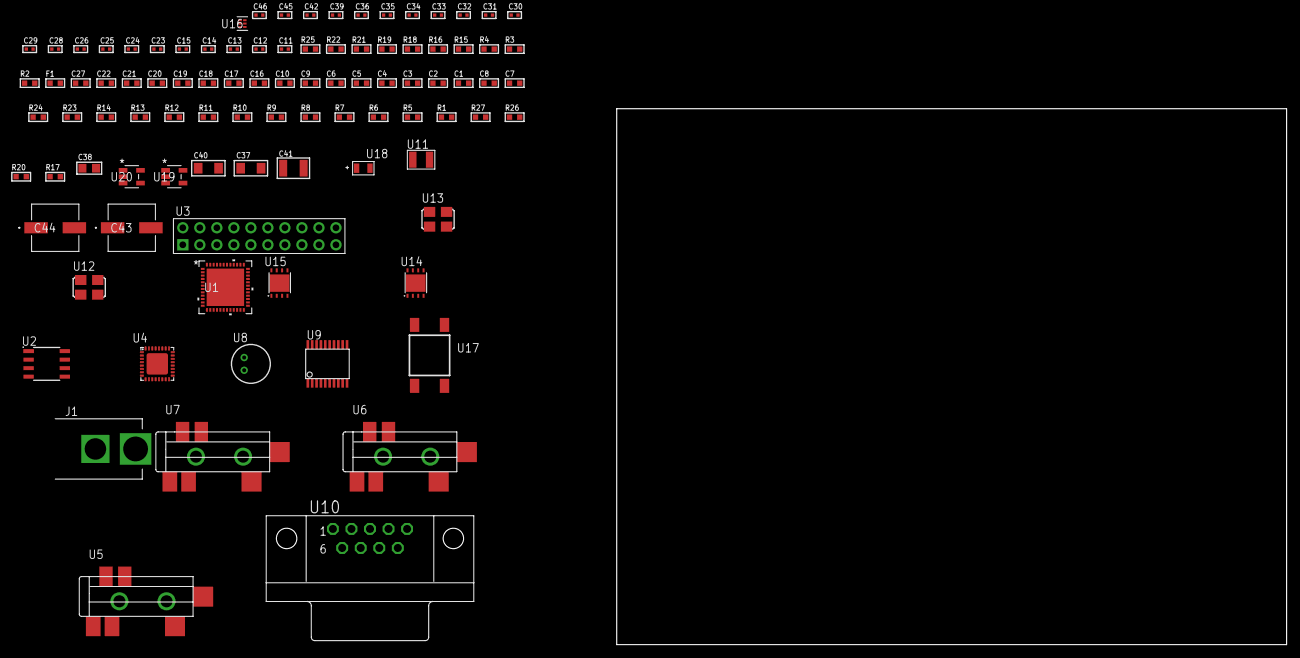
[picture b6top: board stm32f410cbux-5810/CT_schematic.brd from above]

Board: 2 copper layers, 100.0 x 80.0 mm, 95 parts (0 on the bottom side), 67 nets, no tracks yet.

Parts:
C1, C10, C16, C17, C18, C19, C20, C21, C22, C27: 1e-06; C0603
C2, C3, C4, C5, C6: 1e-07; C0603
C7: 4.7e-06; C0603
C8: 2.2e-06; C0603
C9: 1e-08; C0603
C11, C12: 1e-11; C0402
C13, C34, C35, C36, C39, C45, C46: 1e-08; C0402
C14, C15, C23, C24, C25, C26, C28, C29, C30, C31, C32, C33, C42: 1e-07; C0402
C37, C40: 1e-05; C1206
C38: 1e-05; C0805
C41: 1e-05; C1210
C43, C44: 0.0001; EXV-9H
F1: 240.0; L0603
J1: PJ-037B; PJ-037B_PACKAGE
R1, R5, R6, R7, R8, R9, R10, R11, R12, R13, R14, R23, R24: 10000.0; R0603
R2, R19, R22: 1000.0; R0603
R3: 1600.5; R0603
R4: 4700.0; R0603
R15, R16: 1270.0; R0603
R17, R20: 100000.0; R0603
R18: 200.0; R0603
R21: 2231.0; R0603
R25: 9100.0; R0603
R26: 680000.0; R0603
R27: 120000.0; R0603
U1: STM32F410CBU6; UFQFPN48
U2: AT25256B-SSHL-T; SOIC-8
U3: TST-110-05-T-D-RA
U4: SGTL5000XNAA3; QFN-32
U5, U6, U7: SJ-43515TS-SMT-TR
U8: WM-64PCT; WM-64PC
U9: SP3203ECY-L/TR; TSSOP20-I
U10: 182-009-113R531; 182-009-MALE
U11: ABS07-32.768KHZ-7-T
U12: ASFL-24.57MHZ-NCS; ASFL1
U13: ASFL1-25MHZ-NCS; ASFL1
U14, U15: LP3878SDX-ADJ/NOPB; WSON-8
U16: TPS3895ADRYR; SON-6
U17: 4-1437565-2; SW_4-1437565-2
U18: Q65110A2395; LGM67K-G1J2-24-Z
U19, U20: nc7sz125m5x; NC7SZ125M5X

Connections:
CLK_CRYSTAL_U1_3: C11.1, U1.3, U11.1
CLK_CRYSTAL_U1_4: C12.1, U1.4, U11.2
CLK_U1_5: U1.5, U13.3
CLK_U4_21: U4.21, U12.3
GND: C1.2, C2.2, C3.2, C4.2, C5.2, C6.2, C7.2, C8.2, C9.2, C10.2, C11.2, C12.2, C13.2, C14.2, C15.2, C23.2, C24.2, C25.2, C26.2, C27.2, C28.2, C29.2, C32.2, C33.2, C34.2, C35.2, C36.2, C37.2, C38.2, C39.2, C40.2, C41.2, C42.2, C43.2, C44.2, C45.2, C46.2, J1.2, R2.2, R5.2, R14.2, R16.2, R19.2, R22.2, R25.2, R27.2, U1.8, U1.23, U1.35, U1.47, U1.49, U2.4, U3.4, U3.6, U3.8, U3.10, U3.12, U3.14, U3.16, U3.18, U3.20, U4.1, U4.3, U4.7, U4.EXP, U6.1, U7.1, U8.2, U9.18, U10.5, U12.2, U13.2, U14.3, U14.PAD, U15.3, U15.PAD, U16.2, U18.C, U19.2, U19.3, U20.1, U20.3
NET_U1_7: R4.1, U1.7, U20.4
NET_U1_9: C9.1, C10.1, F1.1, U1.9
NET_U1_22: C8.1, U1.22
NET_U1_44: R5.1, U1.44
NET_U1_45: R3.1, U1.45, U18.A
NET_U1_46: R1.1, U1.46, U17.3, U17.4
NET_U2_3: R6.1, U2.3
NET_U2_7: R8.1, U2.7
NET_U3_19: R14.1, U3.19
NET_U4_10: C26.1, U4.10
NET_U4_29: R15.1, U4.29
NET_U4_31: R16.1, U4.31
NET_U5_1: U4.4, U5.1
NET_U5_2: U4.2, U5.2
NET_U5_5: U4.6, U5.5
NET_U6_2: C17.1, U6.2
NET_U6_5: C16.1, U6.5
NET_U7_2: C19.1, C20.1, U7.2
NET_U7_5: C18.1, U7.5
NET_U7_13: C19.2, C20.2
NET_U8_1: C21.1, C22.1, C27.1, U4.16, U8.1
NET_U8_15: C21.2, C22.2
NET_U9_1: C30.1, U9.1
NET_U9_2: C32.1, U9.2
NET_U9_3: C30.2, U9.3
NET_U9_4: C31.1, U9.4
NET_U9_5: C31.2, U9.5
NET_U9_6: C33.1, U9.6
NET_U10_2: U9.14, U10.2
NET_U10_3: U9.17, U10.3
NET_U10_7: U9.13, U10.7
NET_U10_8: U9.16, U10.8
NET_U14_1: C36.1, U14.1
NET_U14_6: R18.2, R19.1, U14.6
NET_U14_8: R17.1, U14.8
NET_U15_1: C39.1, U15.1
NET_U15_6: R21.2, R22.1, U15.6
NET_U15_8: R20.1, U15.8
NET_U16_1: R24.1, R25.1, U16.1
NET_U16_3: R26.2, R27.1, U16.3
NET_U16_4: R23.1, U16.4, U19.4, U20.2
NET_U17_1: R2.1, U17.1, U17.2
PROC_I2S1_CK: U1.15, U4.24
PROC_I2S1_SD: U1.17, U4.26
PROC_I2S1_WS: U1.14, U4.23
PROC_SPI2_MISO: U1.27, U2.2
PROC_SPI2_MOSI: U1.28, U2.5
PROC_SPI2_NSS: R7.1, U1.25, U2.1
PROC_SPI2_SCK: U1.21, U2.6
PROC_SYS_JTCK_SWCLK: R12.1, U1.37, U3.9
PROC_SYS_JTDI: R10.1, U1.38, U3.5
PROC_SYS_JTDO_SWO: U1.39, U3.13
PROC_SYS_JTMS_SWDIO: R11.1, U1.34, U3.7
PROC_SYS_JTRST: R9.1, U1.40, U3.3
PROC_USART1_CTS: U1.32, U9.8
PROC_USART1_RTS: U1.33, U9.10
PROC_USART1_RX: U1.31, U9.11
PROC_USART1_TX: U1.30, U9.7
RST_OUT_U3_SRESET_B: R13.1, U3.15, U19.1
VCC_S1_10V3: C37.1, C40.1, C43.1, C44.1, J1.1, R17.2, R20.2, U14.4, U15.4
VCC_TIER1_1V2: C23.1, C38.1, R18.1, U4.30, U14.5
VCC_TIER1_3V3: C1.1, C2.1, C3.1, C4.1, C5.1, C6.1, C7.1, C13.1, C14.1, C15.1, C24.1, C25.1, C28.1, C29.1, C34.1, C35.1, C41.1, C42.1, C45.1, C46.1, F1.2, R1.2, R3.2, R4.2, R6.2, R7.2, R8.2, R9.2, R10.2, R11.2, R12.2, R13.2, R15.2, R21.1, R23.2, R24.2, R26.1, U1.1, U1.24, U1.36, U1.48, U2.8, U3.1, U3.2, U4.5, U4.20, U9.12, U9.19, U12.4, U13.4, U15.5, U16.6, U19.5, U20.5
